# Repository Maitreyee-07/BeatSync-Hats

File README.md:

# 🎧 Beat Sensing LED Hat

A wearable **music-reactive LED hat** that lights up in sync with surrounding music beats.  
The system uses a **microphone module to detect audio intensity**, processes the signal using an **Arduino Nano**, and drives **WS2812B addressable LEDs** to produce dynamic lighting effects.

This project demonstrates a simple implementation of **real-time audio signal processing on embedded hardware** combined with **programmable LED control**.

---

## ✨ Features

- 🎶 Beat detection using microphone input
- 💡 Dynamic LED patterns synchronized with music
- ⚡ Addressable WS2812B LED control
- 🧠 Arduino Nano based processing
- 👒 Wearable LED hat design

---

## 🧰 Hardware Components

| Component | Description |
|-----------|-------------|
| Arduino Nano | Microcontroller used to process audio signal and control LEDs |
| WS2812B LED Strip | Addressable RGB LEDs for lighting effects |
| Microphone Module | Captures ambient sound/music |
| Power Supply | Battery pack or portable power source |
| Connecting Wires | Circuit connections |

---

## ⚙️ Working Principle

1. The **microphone module** captures ambient sound.
2. The **Arduino Nano reads the analog signal** from the microphone.
3. The program monitors the **audio amplitude**.
4. When the signal exceeds a defined **threshold**, it is interpreted as a **beat**.
5. The **WS2812B LEDs respond with lighting effects** such as flashes or color transitions.

This enables the LEDs on the hat to **react to music in real time**.

---
## 🖼 System Overview

Microphone → Arduino Nano → WS2812B LEDs
(Audio) (Processing) (Lighting Effects)

---

## 🔌 Circuit Connections

| Device | Arduino Pin |
|------|------|
| Microphone OUT | A0 |
| WS2812B Data | D6 |
| VCC | 5V |
| GND | GND |

*(Pin configuration may vary depending on the implementation.)*

---

## 💻 Software Requirements

- Arduino IDE
- FastLED library or Adafruit NeoPixel library

Install required libraries using the **Arduino Library Manager**.

---

## 🚀 How to Run

1. Clone the repository
git clone https://github.com/Maitreyee-07/BeatSync-Hats.git

2. Open the Arduino sketch in **Arduino IDE**

3. Install required LED libraries

4. Upload the code to **Arduino Nano**

5. Power the system and play music near the hat 🎶

---

## 🔧 Future Improvements

- FFT based beat detection
- Multiple LED animation modes
- Adjustable sensitivity
- Bluetooth music synchronization
- Custom wearable PCB

---

## 👩‍💻 Author

**Maitreyee Kumbhojkar**  
Electrical Engineering, IIT Dharwad  

GitHub: https://github.com/Maitreyee-07

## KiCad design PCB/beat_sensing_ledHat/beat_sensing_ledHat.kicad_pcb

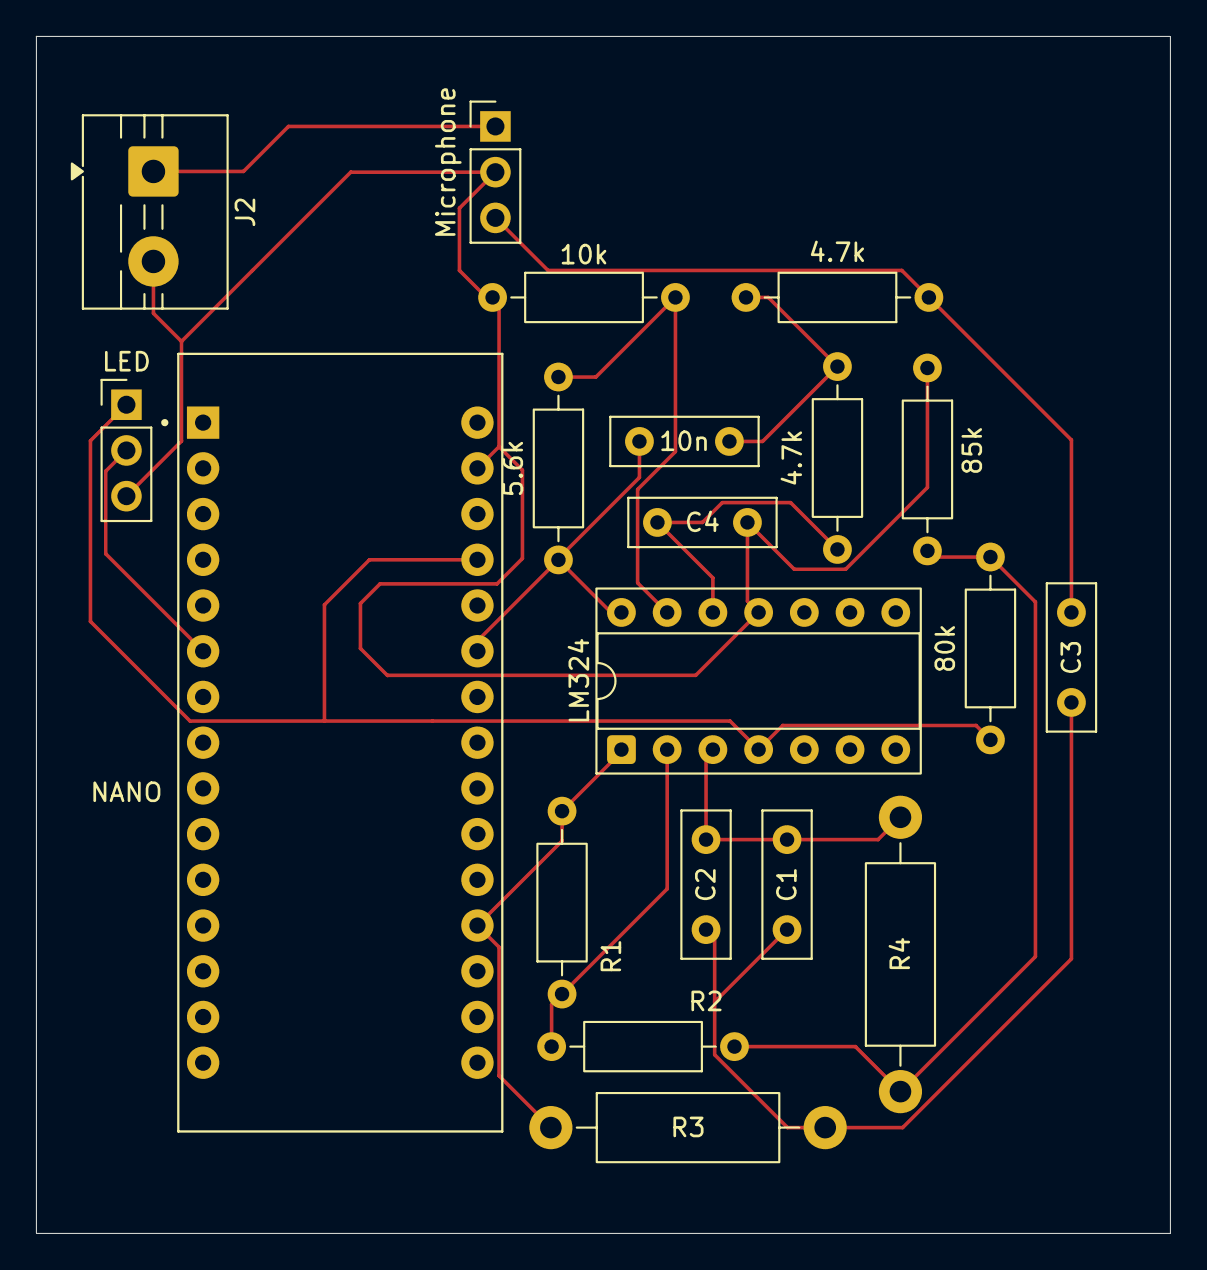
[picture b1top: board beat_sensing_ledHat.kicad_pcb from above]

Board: 2 copper layers, 63.0 x 66.5 mm, 20 parts (0 on the bottom side), 13 nets.

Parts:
4.7k, 4.7k#2: 4.7k; R_Axial_DIN0207_L6.3mm_D2.5mm_P10.16mm_Horizontal
5.6k: 5.6k; R_Axial_DIN0207_L6.3mm_D2.5mm_P10.16mm_Horizontal
10k: 10k; R_Axial_DIN0207_L6.3mm_D2.5mm_P10.16mm_Horizontal
10n: 10n; C_Disc_D8.0mm_W2.5mm_P5.00mm
80k: 80k; R_Axial_DIN0207_L6.3mm_D2.5mm_P10.16mm_Horizontal
85k: 85k; R_Axial_DIN0207_L6.3mm_D2.5mm_P10.16mm_Horizontal
C1, C2, C3, C4: 10n; C_Disc_D8.0mm_W2.5mm_P5.00mm
J2: Screw_Terminal_01x02; TerminalBlock_MaiXu_MX126-5.0-02P_1x02_P5.00mm
LED: LED; PinHeader_1x03_P2.54mm_Vertical
LM324: LM324; DIP-14_W7.62mm_Socket
Microphone: Microphone; PinHeader_1x03_P2.54mm_Vertical
NANO: ARDUINO_NANO; MODULE_ARDUINO_NANO
R1: 4.7k; R_Axial_DIN0207_L6.3mm_D2.5mm_P10.16mm_Horizontal
R2: 10k; R_Axial_DIN0207_L6.3mm_D2.5mm_P10.16mm_Horizontal
R3, R4: 2.2k; R_Axial_DIN0411_L9.9mm_D3.6mm_P15.24mm_Horizontal

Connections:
1.65V: 80k.1, 85k.2, R2.1, R4.1
GND: 10k.1, 85k.1, C4.1, J2.2, LED.3, LM324.11, Microphone.2, NANO.29 (GND_29)
HP: LM324.1, NANO.19 (A0), R1.2, R3.1
LP: 5.6k.2, 10n.1, LM324.14, NANO.25 (A6)
unnamed: C1.1, C2.1, C3.2, R3.2
unnamed: C1.2, C2.2, LM324.3, R4.2
unnamed: 4.7k#2.2, C4.2, LM324.12
unnamed: 4.7k.2, 4.7k#2.1, 10n.2
unnamed: LM324.2, R1.1, R2.2
unnamed: 5.6k.1, 10k.2, LM324.13
unnamed: 4.7k.1, C3.1, Microphone.3
unnamed: LED.2, NANO.6 (D3)
VBATT: 80k.2, J2.1, LED.1, LM324.4, Microphone.1, NANO.27 (+5V)

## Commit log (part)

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2026-03-09 Add SoundReactive functionality for LED control
2026-03-16 Revise README to include detailed project overview
    Expanded project details, features, and setup instructions for the Beat Sensing LED Hat.
2026-03-16 Create demo
2026-03-16 Remove prototype section from README
    Removed prototype section and related images from README.
2026-03-17 PCB Folder
    The folder for PCB designing
2026-03-30 PCB Designing
